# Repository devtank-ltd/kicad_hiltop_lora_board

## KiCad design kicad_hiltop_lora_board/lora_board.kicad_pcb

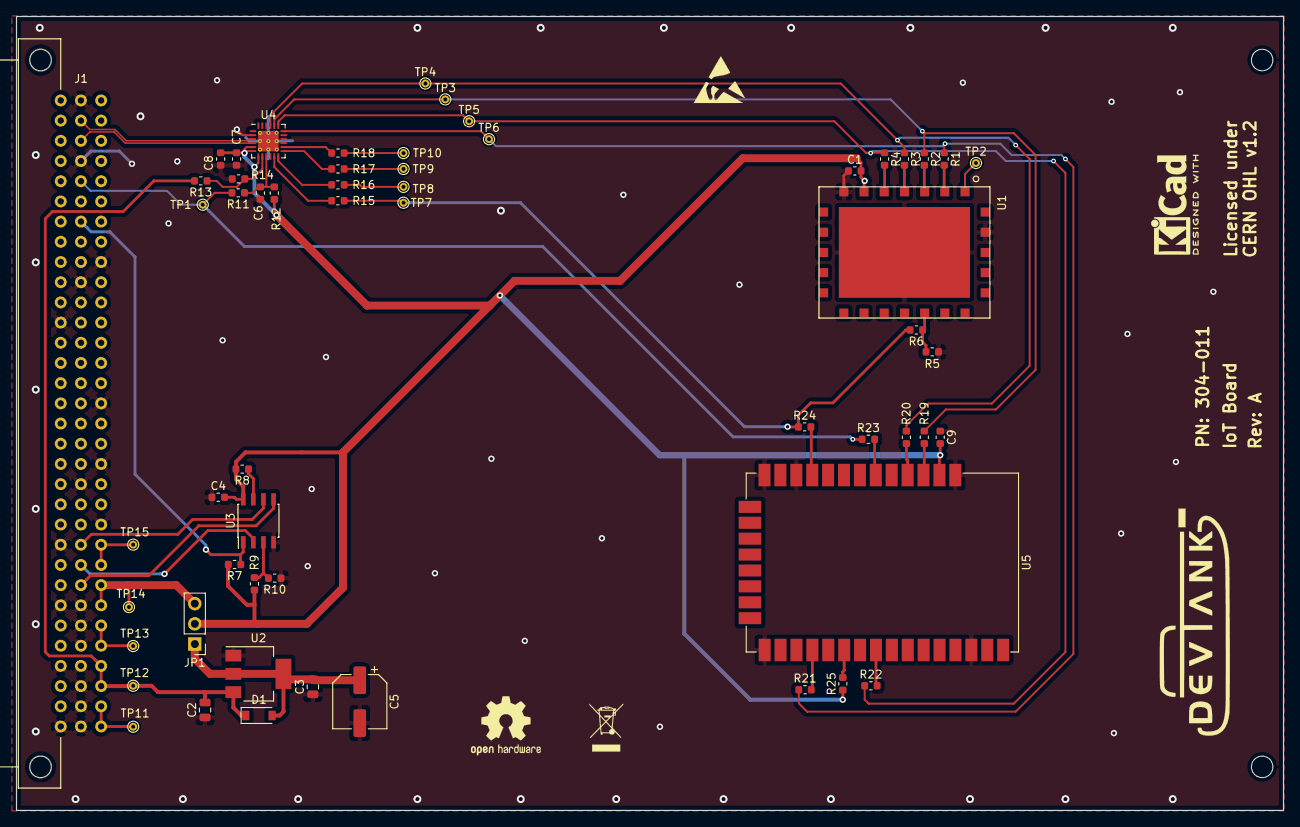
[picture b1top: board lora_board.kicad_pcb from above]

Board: 2 copper layers, 159.4 x 99.9 mm, 57 parts (0 on the bottom side), 44 nets.

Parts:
C1, C4, C8, C9: 100nF; C_0603_1608Metric
C2, C3: 10uF; C_0805_2012Metric
C5: 100uF; CP_Elec_6.3x7.7
C6: DNF; C_0603_1608Metric
C7: 4.7uF; C_0603_1608Metric
D1: MBR230LSFT1G; D_SOD-123
J1: Conn_03x32_DIN41612; Socket_DIN41612-CaseC1-full-Male-96Pin-3rows_correct
JP1: Jumper_NC_Dual; PinHeader_1x03_P2.54mm_Vertical
R1, R2, R3, R4, R6, R11, R15: 0R; R_0603_1608Metric
R5, R10, R12, R16, R17, R18, R19, R20, R21, R22, R23, R24, R25: DNF; R_0603_1608Metric
R7: 10K; R_0603_1608Metric
R8, R9: 4K7; R_0603_1608Metric
R13: 24K; R_0603_1608Metric
R14: 47K; R_0603_1608Metric
TP1, TP2, TP3, TP4, TP5, TP6, TP7, TP8, TP9, TP10, TP11, TP12, TP13, TP14, TP15: Test_Point; TestPoint_THTPad_D1.0mm_Drill0.5mm
U1: ERIC-LORA; eRIC-LoRa_RF_Module
U2: LD1117S33TR_SOT223; SOT-223-3_TabPin2
U3: AT25DN512CSSHF-B; SOIC-8_3.9x4.9mm_P1.27mm
U4: CP2102N-A01-GQFN24; QFN-24-1EP_4x4mm_P0.5mm_EP2.6x2.6mm_ThermalVias
U5: XBee_SMT; Digi_XBee_SMT

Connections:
+3V3: C1.2, C4.2, C7.1, C8.1, C9.2, JP1.2, R7.2, R8.2, R9.2, R12.2, R25.1, U1.6, U3.8, U4.5, U4.6, U4.7, U5.2
+3V3_BP: J1.7c, J1.8c, JP1.3, TP14.1
+3V3_LOC: C3.2, C5.1, D1.2, JP1.1, U2.2
+5V: C2.2, D1.1, J1.3c, J1.4c, R13.2, TP12.1, U2.3
+12V: J1.1c, J1.2c, TP11.1
-5V: J1.5c, J1.6c, TP13.1
/HOST_CTS: R1.1, R21.1, TP6.1, U4.18
/HOST_RTS: R4.1, R22.1, TP5.1, U4.19
/HOST_RX: R2.1, R19.1, TP3.1, U4.20
/HOST_SLEEP: R6.2, R15.1, R24.1, TP7.1
/HOST_TX: R3.1, R20.1, TP4.1, U4.21
/LORA_CTS: R1.2, U1.2
/LORA_RTS: R4.2, U1.5
/LORA_RX: R2.2, U1.3
/LORA_SLEEP: R5.1, R6.1, U1.17
/LORA_TX: R3.2, U1.4
/PORT_SEL: J1.26b, R7.1, U3.1
/RESET: J1.28b, R11.2, R23.1, TP1.1
/SPI0_CLK: J1.10b, U3.6
/SPI0_MISO: J1.9b, U3.2
/SPI0_MOSI: J1.8b, U3.5
/USB_DATA_N: J1.30b, U4.4
/USB_DATA_P: J1.31b, U4.3
/USB_Debug/GPIO0: R18.1, TP10.1
/USB_Debug/GPIO1: R17.1, TP9.1
/USB_Debug/GPIO2: R16.1, TP8.1
ADJ_DC: J1.9c, J1.10c, TP15.1
GND: C1.1, C2.1, C3.1, C4.1, C5.2, C6.2, C7.2, C8.2, C9.1, J1.1a, J1.1b, J1.2b, J1.3b, J1.4a, J1.4b, J1.5b, J1.6b, J1.7a, J1.7b, J1.10a, J1.11c, J1.13b, J1.14c, J1.17c, J1.21a, J1.23b, J1.24c, J1.29b, J1.32b, R5.2, R10.1, R14.1, U1.7, U1.23, U2.1, U3.4, U4.2, U4.25, U5.1, U5.11, U5.13, U5.22, U5.35
unnamed: C6.1, R11.1, R12.1, U4.9
unnamed: R8.1, U3.7
unnamed: R9.1, R10.2, U3.3
unnamed: R13.1, R14.2, U4.8
unnamed: R15.2, U4.11
unnamed: R16.2, U4.12
unnamed: R17.2, U4.13
unnamed: R18.2, U4.14
unnamed: R19.2, U5.3
unnamed: R20.2, U5.4
unnamed: R21.2, U5.25
unnamed: R22.2, U5.29
unnamed: R23.2, U5.6
unnamed: R24.2, U5.10
unnamed: R25.2, U5.27
unnamed: TP2.1, U1.1

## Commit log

2019-11-21 Setup common libraries for my Kicad project.
2019-11-21 Setup initial project
2020-02-09 finished design - Rev A

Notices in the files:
kicad_hiltop_lora_board/lora_board.kicad_pcb:
Licensed under
CERN OHL v1.2
